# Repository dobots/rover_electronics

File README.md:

# Rover_electronics
Dobots circuit schematics and PCB designs for the rover robots.

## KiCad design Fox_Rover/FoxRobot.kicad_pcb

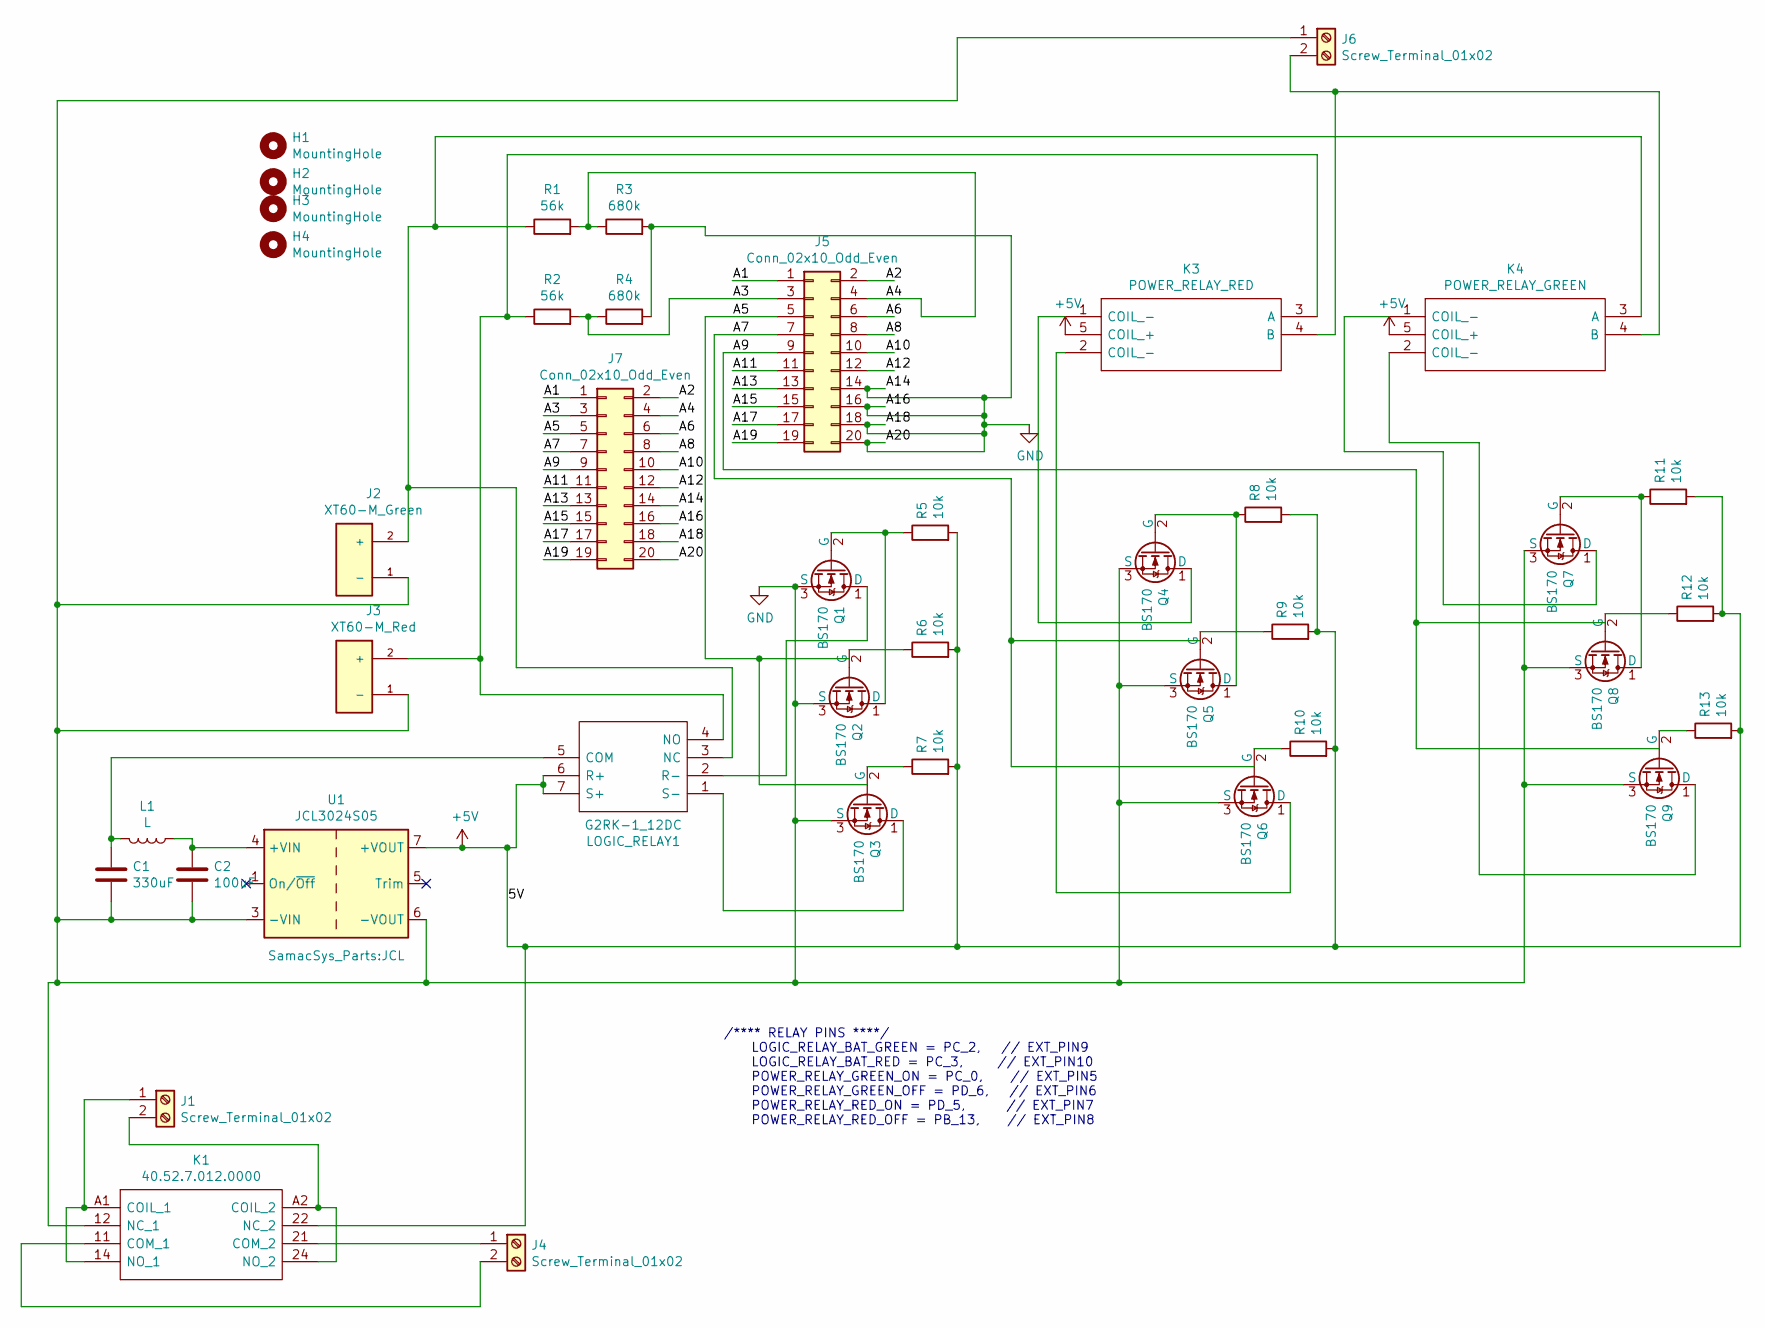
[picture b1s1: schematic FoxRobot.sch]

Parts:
C1: 330uF; C_Disc_D7.5mm_W2.5mm_P5.00mm
C2: 100uF; C_Disc_D7.5mm_W2.5mm_P5.00mm
H1, H2, H3, H4: MountingHole; MountingHole_3.2mm_M3_ISO7380_Pad_TopBottom
J1, J4, J6: Screw_Terminal_01x02; TerminalBlock_Phoenix_MKDS-1,5-2-5.08_1x02_P5.08mm_Horizont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
J2: XT60-M_Green; Solder_Pads; PARTREV 1.2
J3: XT60-M_Red; Solder_Pads; PARTREV 1.2
J5, J7: Conn_02x10_Odd_Even; PinSocket_2x10_P2.54mm_Vertical
K1: 40.52.7.012.0000; 405270120000; Manufacturer_Part_Number 40.52.7.012.0000
K3: POWER_RELAY_RED; ADJH23005; Manufacturer_Part_Number ADJH23005; Mouser Part Number 667-ADJH23005
K4: POWER_RELAY_GREEN; ADJH23005; Manufacturer_Part_Number ADJH23005; Mouser Part Number 667-ADJH23005
L1: L; L_Radial_D10.0mm_P5.00mm_Fastron_07M
LOGIC_RELAY1: G2RK-1_12DC; G2RK112DC; Manufacturer_Part_Number G2RK-1 12DC
Q1, Q2, Q3, Q4, Q5, Q6, Q7, Q8, Q9: BS170; TO-92_Inline
R1, R2: 56k; R_Axial_DIN0207_L6.3mm_D2.5mm_P10.16mm_Horizontal
R3, R4: 680k; R_Axial_DIN0207_L6.3mm_D2.5mm_P10.16mm_Horizontal
R5, R6, R7, R8, R9, R10, R11, R12, R13: 10k; R_Axial_DIN0207_L6.3mm_D2.5mm_P10.16mm_Horizontal
U1: JCL3024S05; JCL

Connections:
+5V: K1.22 (NC_2), K3.5 (COIL_+), K4.5 (COIL_+), LOGIC_RELAY1.6 (R+), LOGIC_RELAY1.7 (S+), R5.2, R6.2, R7.2, R8.2, R9.2, R10.2, R11.2, R12.2, R13.2, U1.7 (+VOUT); also elsewhere on the board
/A1: J5.1, J7.1
/A2: J5.2, J7.2
/A3: J5.3, J7.3, R2.2, R4.1
/A4: J5.4, J7.4, R1.2, R3.1
/A5: J5.5, J7.5
/A6: J5.6, J7.6
/A7: J5.7, J7.7
/A8: J5.8, J7.8
/A9: J5.9, J7.9
/A10: J5.10, J7.10
/A11: J5.11, J7.11
/A12: J5.12, J7.12
/A13: J5.13, J7.13
/A15: J5.15, J7.15
/A17: J5.17, J7.17
/A19: J5.19, J7.19
GND: C1.2, C2.2, J2.1 (-), J3.1 (-), J5.14, J5.16, J5.18, J5.20, J6.1, J7.14, J7.16, J7.18, J7.20, K1.12 (NC_1), Q1.3 (S), Q2.3 (S), Q3.3 (S), Q4.3 (S), Q5.3 (S), Q6.3 (S), Q7.3 (S), Q8.3 (S), Q9.3 (S), R3.2, R4.2, U1.3 (-VIN), U1.6 (-VOUT)
unnamed 18: C1.1, L1.2, LOGIC_RELAY1.5 (COM); also elsewhere on the board
unnamed: C2.1, L1.1, U1.4 (+VIN)
unnamed: J1.1, K1.14 (NO_1), K1.A1 (COIL_1)
unnamed: J1.2, K1.24 (NO_2), K1.A2 (COIL_2)
unnamed 22: J2.2 (+), K4.3 (A), LOGIC_RELAY1.3 (NC), R1.1; also elsewhere on the board
unnamed 23: J3.2 (+), K3.3 (A), LOGIC_RELAY1.4 (NO), R2.1; also elsewhere on the board
unnamed: J4.1, K1.21 (COM_2)
unnamed: J4.2, K1.11 (COM_1)
unnamed: J6.2, K3.4 (B), K4.4 (B)
unnamed 27: LOGIC_RELAY1.1 (S-), Q3.1 (D); also elsewhere on the board
unnamed 28: LOGIC_RELAY1.2 (R-), Q1.1 (D); also elsewhere on the board
unnamed: K3.1 (COIL_-), Q4.1 (D)
unnamed: K3.2 (COIL_-), Q6.1 (D)
unnamed: K4.1 (COIL_-), Q7.1 (D)
unnamed: K4.2 (COIL_-), Q9.1 (D)
unnamed: Q1.2 (G), Q2.1 (D), R5.1
unnamed: Q2.2 (G), R6.1
unnamed: Q3.2 (G), R7.1
unnamed: Q4.2 (G), Q5.1 (D), R8.1
unnamed: Q5.2 (G), R9.1
unnamed: Q6.2 (G), R10.1
unnamed: Q7.2 (G), Q8.1 (D), R11.1
unnamed: Q8.2 (G), R12.1
unnamed: Q9.2 (G), R13.1

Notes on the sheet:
/**** RELAY PINS ****/ LOGIC_RELAY_BAT_GREEN = PC_2, // EXT_PIN9 LOGIC_RELAY_BAT_RED = PC_3, // EXT_PIN10 POWER_RELAY_GREEN_ON = PC_0, // EXT_PIN5 POWER_RELAY_GREEN_OFF = PD_6, // EXT_PIN6 POWER_RELAY_RED_ON = PD_5, // EXT_PIN7 POWER_RELAY_RED_OFF = PB_13, // EXT_PIN8

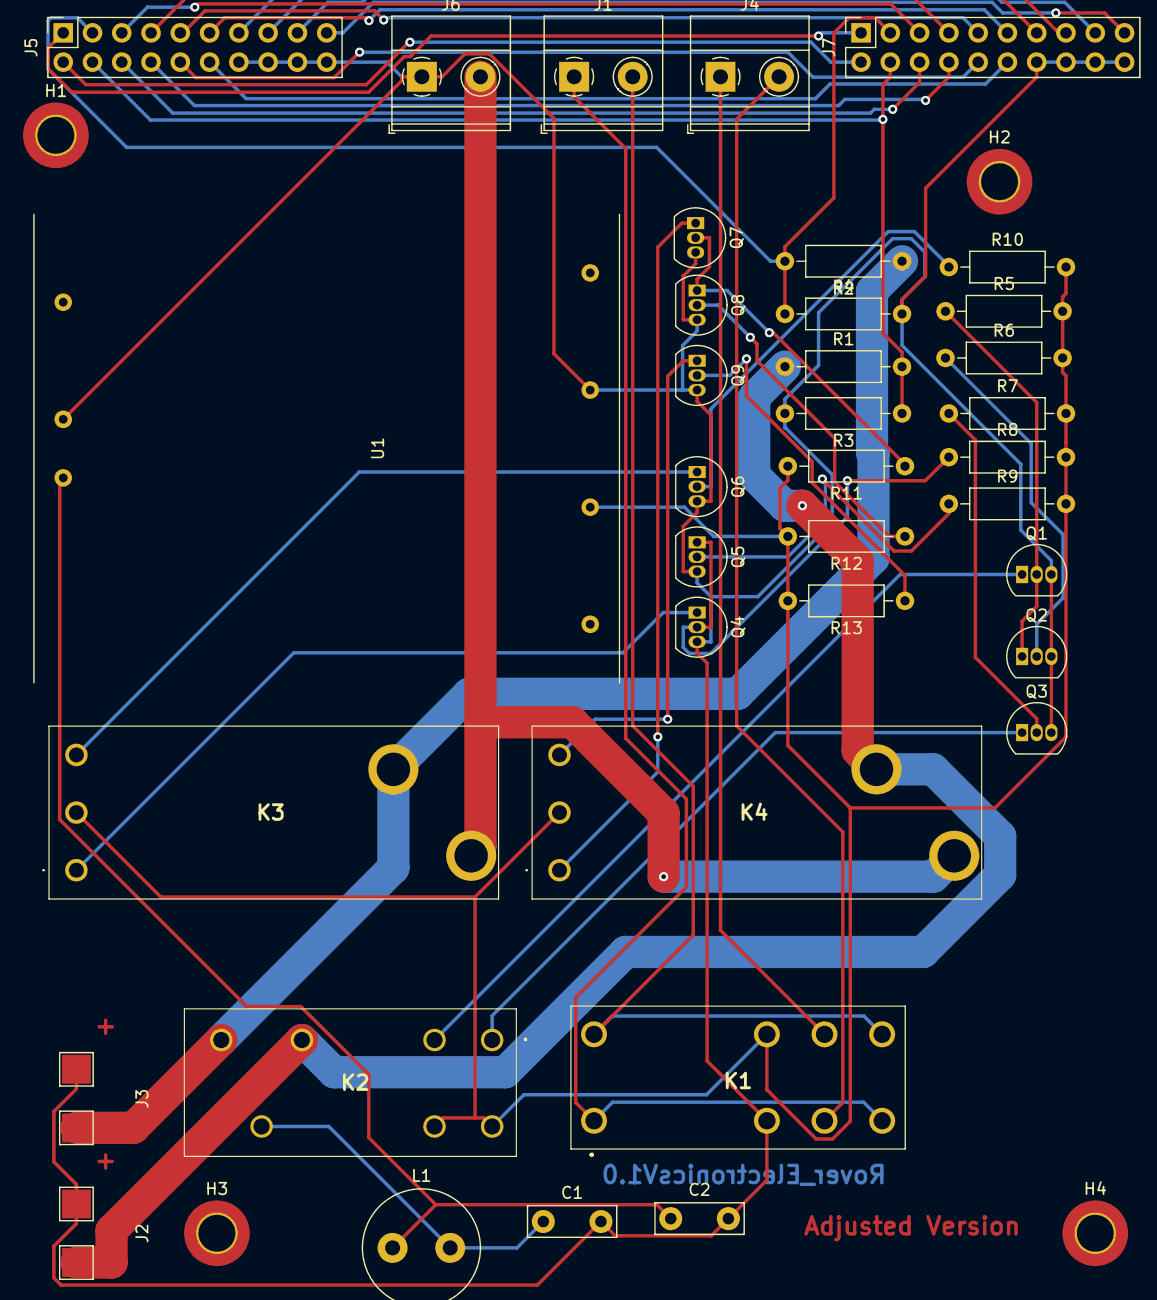
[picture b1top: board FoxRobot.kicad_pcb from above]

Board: 2 copper layers, 41 parts (0 on the bottom side), 42 nets.

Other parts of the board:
K2: G2RK-1_12DC; G2RK112DC

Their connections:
+5V: K2.6, K2.7; also elsewhere on the board
unnamed 18: K2.5; also elsewhere on the board
unnamed 22: K2.3; also elsewhere on the board
unnamed 23: K2.4; also elsewhere on the board
unnamed 27: K2.1; also elsewhere on the board
unnamed 28: K2.2; also elsewhere on the board

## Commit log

2021-11-08 Added the Fox Rover Schematics
2021-11-10 Added an extra header output to the schematics and started initial PCB designs
2021-11-10 PCB design suitable
2021-11-10 Adjusted for mounting platforms
    Adjust sizing for lower pricing
2021-11-17 Added The original Fox Design
    Still needs to be finalized
2021-11-17 Added Schem
2021-11-19 Added the filter capacitor and coil.
2022-02-07 Adjusted libraries pathing
2022-02-07 Adjusting libraries
